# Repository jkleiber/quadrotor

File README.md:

# Quadrotor

This is a project for the hardware and software of a quadcopter.

## Quadcopter 3D CAD
The quadcopter is 3D printed and all CAD work is done in OnShape in [this project](https://cad.onshape.com/documents/413384f17bd393d247c9b79e/w/f46ad751ac408daab1c55c23/e/428b8b34f12af24e5b48da17?renderMode=0&uiState=62fc49f3bee5066f5bad792f)

## Control Simulation GUI

The control simulator uses ImGui to allow for real-time data viewing and parameter tuning. Below is a snapshot of the GUI:

## Hardware

A custom flight controller made in KiCAD exists in the `hardware/` directory. This is a breakout board for a Teensy, BNO055 IMU, a GPS module and the PWM outputs for the ESCs.

## Gazebo Simulation

There is a gazebo simulation environment in the `gazebo-sim/` directory. It is somewhat functional, but more work has been put into the control simulation GUI. The current gazebo settings aren't configured for the actual drone.

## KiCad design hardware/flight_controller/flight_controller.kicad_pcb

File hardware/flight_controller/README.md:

# Flight Controller

## Development
The latest version is version 1.1. 

## Errata

### Version 1.1
- On both of the left motors, signal is labeled as ground and vice versa on the PWM output pins to the ESCs. Note made of this for future designs.

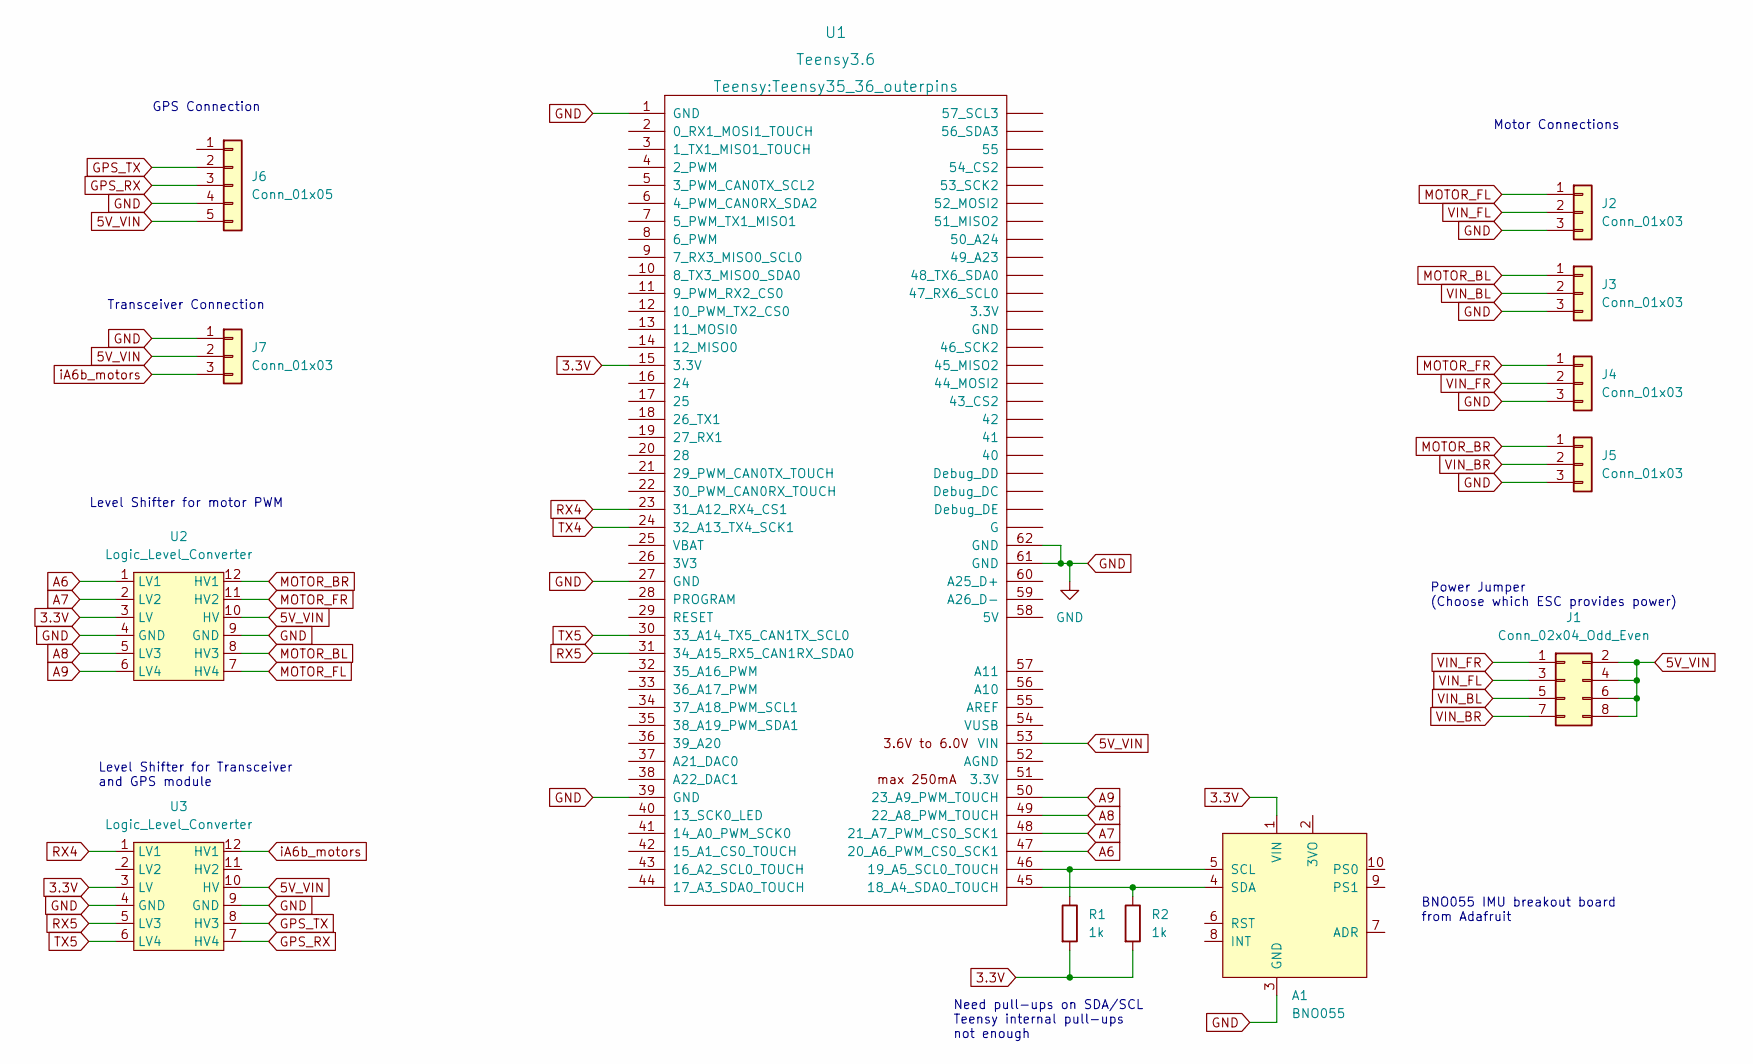
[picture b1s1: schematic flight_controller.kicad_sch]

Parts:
A1: BNO055
J1: Conn_02x04_Odd_Even; PinHeader_2x04_P2.54mm_Vertical
J2, J3, J4, J5: Conn_01x03; PinHeader_1x03_P2.54mm_Vertical
J6: Conn_01x05; PinSocket_1x05_P2.54mm_Vertical
J7: Conn_01x03; PinSocket_1x03_P2.54mm_Vertical
R1, R2: 1k; R_Axial_DIN0207_L6.3mm_D2.5mm_P15.24mm_Horizontal
U1: Teensy3.6; Teensy35_36_outerpins
U2, U3: Logic_Level_Converter

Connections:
3.3V: A1.1 (VIN), R1.2, R2.2, U1.15 (3.3V), U2.3 (LV), U3.3 (LV)
5V_VIN: J1.2, J1.4, J1.6, J1.8, J6.5, J7.2, U1.53 (VIN), U2.10 (HV), U3.10 (HV)
A6: U1.47 (20_A6_PWM_CS0_SCK1), U2.1 (LV1)
A7: U1.48 (21_A7_PWM_CS0_SCK1), U2.2 (LV2)
A8: U1.49 (22_A8_PWM_TOUCH), U2.5 (LV3)
A9: U1.50 (23_A9_PWM_TOUCH), U2.6 (LV4)
GND: A1.3 (GND), J2.3, J3.3, J4.3, J5.3, J6.4, J7.1, U1.1 (GND), U1.27 (GND), U1.39 (GND), U1.61 (GND), U1.62 (GND), U2.4 (GND), U2.9 (GND), U3.4 (GND), U3.9 (GND)
GPS_RX: J6.3, U3.7 (HV4)
GPS_TX: J6.2, U3.8 (HV3)
MOTOR_BL: J3.1, U2.8 (HV3)
MOTOR_BR: J5.1, U2.12 (HV1)
MOTOR_FL: J2.1, U2.7 (HV4)
MOTOR_FR: J4.1, U2.11 (HV2)
unnamed: A1.4 (SDA), R2.1, U1.45 (18_A4_SDA0_TOUCH)
unnamed: A1.5 (SCL), R1.1, U1.46 (19_A5_SCL0_TOUCH)
RX4: U1.23 (31_A12_RX4_CS1), U3.1 (LV1)
RX5: U1.31 (34_A15_RX5_CAN1RX_SDA0), U3.5 (LV3)
TX4: U1.24 (32_A13_TX4_SCK1)
TX5: U1.30 (33_A14_TX5_CAN1TX_SCL0), U3.6 (LV4)
VIN_BL: J1.5, J3.2
VIN_BR: J1.7, J5.2
VIN_FL: J1.3, J2.2
VIN_FR: J1.1, J4.2
iA6b_motors: J7.3, U3.12 (HV1)

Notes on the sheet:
Need pull-ups on SDA/SCL Teensy internal pull-ups not enough
Transceiver Connection
Level Shifter for motor PWM
Power Jumper (Choose which ESC provides power)
Level Shifter for Transceiver and GPS module
BNO055 IMU breakout board from Adafruit
Motor Connections
GPS Connection

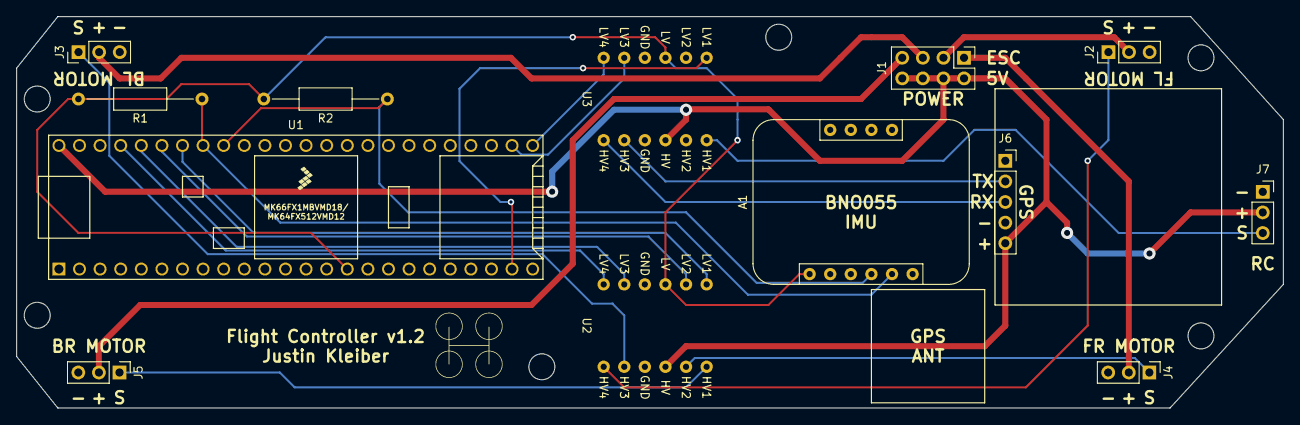
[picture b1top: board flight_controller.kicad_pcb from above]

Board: 2 copper layers, 156.2 x 48.3 mm, 13 parts (0 on the bottom side), 23 nets.

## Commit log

2021-08-26 Creates project workflow scripts, makes quadcopter plugin work in gazebo, makes a really bad bang-bang controller for the drone that keeps it at the right height as long as the drone is set up perfec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
2021-08-26 Renames some stuff quadrotor_fc to indicate flight controller
2022-05-30 Begins work on quadcopter firmware, starting with the interface between the FS-iA6b receiver and the Teensy 3.6 using IBusBM
2022-05-30 Updates the comments for the quadrotor firmware
2022-06-01 Initial calibration, testing and flight control.
    Flight control is a disaster at the moment. Need to probably make a model and try to control that
2022-06-12 Begins to work on simulating the control system for the quadcopter. Makes a safety mode for the quadcopter to avoid crashes causing more damage than they should
2022-06-14 changed the moment calculation to not be blatantly wrong
2022-06-14 Creates a height PID that does decently well at stabilizing the drone's height. About 0.15m ss error
2022-06-19 Adds logging and data analysis tool for simulation. Also creates initial PID attitude control that works in sim. Need to smooth out the control signal and add a delay to the motor throttle dynamics t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
2022-06-19 Hopefully removes jupyter notebook from language stats on Github, as this project is mostly C++
2022-06-21 Adds slew rate limit and makes PID controllers less aggressive
2022-06-28 Applies simulated control gains to the firmware. Need to test on quadcopter
2022-07-03 Adds SD logging to flight control firmware, but will only be able to test when the FC is rewired/PCB is ordered due to space issues
2022-07-06 Begins PCB project for flight controller
2022-07-09 PCB design for flight controller is basically complete. Need to verify and have fun with the design before ordering
2022-07-09 Finalizes and orders flight controller PCB
2022-07-11 Design v1 sent to JLC PCB
2022-07-23 Updates FC board to v1.1 due to footprint size error
    Need to choose different parts and include BOM for hardware
2022-07-25 Fixes PCB for v1.1, gets logging working in firmawre, adds data viewing in jupyter notebooks
2022-07-28 Orders PCB, fixes IMU polarity for roll in the firmware after testing
2022-07-28 Saves PCB design
2022-07-29 Adds PID control display tools
2022-08-08 Improves control simulation by making it a GUI based on ImGui
    Reorganizes project to be more aligned with the CMake standards
2022-08-10 Adds Eigen, makes imgui a static library, gets the GUI to compile on windows.
    Need to check that the GUI still works on linux
2022-08-10 Makes the compilation platform specific since it is fragile. Also Eigen didn't get extracted correctly on windows so this adds the core library that was somehow missing
2022-08-11 Adds implot for graphing but it's not quite ready yet
2022-08-11 Gets GUI graphs to work
2022-08-11 Makes beginning skeleton for tuning control parameters in the GUI
2022-08-12 Adds windows includes for math utilities
2022-08-13 Adds gain tuning to the GUI and saves the default gains to a file
2022-08-14 Adds ability to configure quadcopter params but needs to add saving
2022-08-14 Adds saving the quadcopter parameters. Now need to allow adjustment / toggle noise levels
2022-08-15 Refactors code to follow consistent naming convention for functions.
    Adds height and XY plot
2022-08-17 Updates README and allows configuration files to be tracked
2022-08-20 Allows build configuration to be tracked
2023-01-22 Wired up the quadcopter with v1.1 and tried to fly it. Control loops still need tuning, but auto-stop works
    Begins updated v1.2 PCB (just errata of v1.1 for now) and need to improve simulation with initial system ID
    Weighed drone and it weighs 1 kg (1001 g)
2023-03-25 PID gain tuning, but the front right motor is getting hot and might be a problem
2023-03-27 Using rate based control works better
2023-04-01 More filtering and better analysis
2023-04-02 Switching back to rate mode to see if this can fly. It looks like the rate PIDs are actually too slow
2023-04-04 Converts everything to degrees, also makes utils for PWM
2023-04-07 More PID tuning... The frame may need to be re-thought to get better performance
2023-04-20 Found bug in angular rate measurement logic, switching to pypoetry for notebooks
2023-05-21 Flight 132 test and code updates (pre and post test)
2023-05-29 Flight testing with tuned down gains, made gains const, downgraded tornado to 6.1 in order to get jupyter working in poetry
2023-05-29 Refactors attitude controller to a separate class
    constants moved to a separate file and gains tuned some more.
2023-06-22 Optimized throttle curve
2023-06-24 Thrust testing only, attitude control is disabled
2025-09-26 refactors simulation into gazebo-sim
2025-09-26 Prepares gitattributes for UE5 project
2025-09-26 Base world for quadrotor sim in unreal engine 5
2025-09-28 Makes the simulator camera track the quadcopter
    next up: actually simulate quadcopter motion
2025-09-28 reorganizes script and analysis file structure
2025-09-28 begins modularization effort of control sim
2025-09-28 Removes random build files and ignores them in the future
2025-10-14 Decouples dynamics from the sim loop
2025-10-14 Begins migrating autopilot from arduino to C++ to allow for sim on real software
2025-11-17 Sets up quadcopter simulator to be independent of ImGui and control loops
2025-11-17 pulls in quadcopter dynamics updates
2025-11-17 Gets quadcopter flying poorly from an altitude control perspective
